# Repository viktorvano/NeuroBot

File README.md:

# NeuroBot
This is open source robot with a deep neural network.
Deep Neural Network can be configured by a file content.

Training Data are in "training.txt".

Topology is in "topology.txt".

Demo video: https://www.youtube.com/watch?v=UL9_z_reCno

Android App: https://play.google.com/store/apps/details?id=com.cyberpunktech.RobotController.app

If the content of "weights.txt" file is deleted, the neural network automatically retrain itself again.
If the number of weights in the weights.txt file matches with topology, the Neural Network just loads them, and runs.

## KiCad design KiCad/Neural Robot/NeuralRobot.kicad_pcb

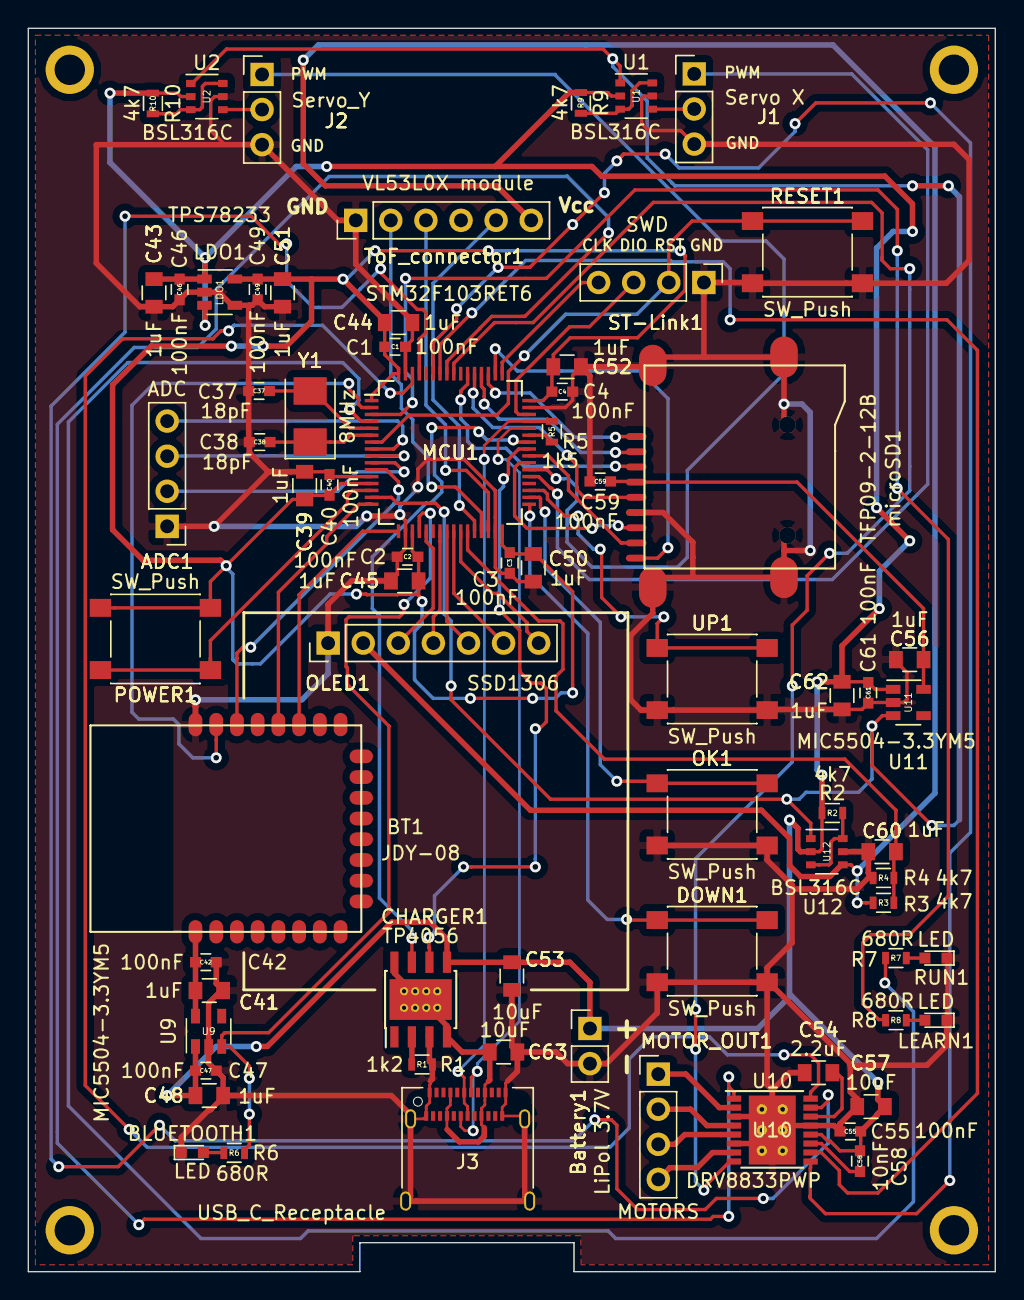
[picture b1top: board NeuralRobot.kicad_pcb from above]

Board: 2 copper layers, 70.0 x 90.0 mm, 70 parts (0 on the bottom side), 71 nets.

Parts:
ADC1: ADC; Socket_Strip_Straight_1x04_Pitch2.54mm
BLUETOOTH1: LED; LED_0603
BT1: JDY-08; JDY-08_module
Battery1: LiPol 3.7V; Socket_Strip_Straight_1x02_Pitch2.54mm
C1, C2, C3, C4, C40, C42, C46, C47, C49, C55, C59, C61: 100nF; C_0603
C37, C38: 18pF; C_0603
C39, C41, C43, C44, C45, C48, C50, C51, C52, C56, C60, C62: 1uF; C_0805
C53, C57, C63: 10uF; C_0805
C54: 2.2uF; C_0805
C58: 10nF; C_0603
CHARGER1: TP4056; HTSOP-8-1EP_3.9x4.9mm_Pitch1.27mm_ThermalVias_LargeCopper
DOWN1: SW_Push; SW_SPST_PTS645
J1: Servo X; Socket_Strip_Straight_1x03_Pitch2.54mm
J2: Servo_Y; Socket_Strip_Straight_1x03_Pitch2.54mm
J3: USB_C_Receptacle; USB_C_Receptacle_Amphenol_12401610E4-2A
LDO1: TPS78233; SOT-23-5
LEARN1: LED; LED_0603
MCU1: STM32F103RET6; LQFP-64_10x10mm_Pitch0.5mm
MOTOR_OUT1: MOTORS; Socket_Strip_Straight_1x04_Pitch2.54mm
OK1: SW_Push; SW_SPST_PTS645
OLED1: SSD1306; Socket_Strip_Straight_1x07_Pitch2.54mm
POWER1: SW_Push; SW_SPST_PTS645
R1: 1k2; R_0603
R2, R3, R4, R9, R10: 4k7; R_0603
R5: 1k5; R_0603
R6, R7, R8: 680R; R_0603
RESET1: SW_Push; SW_SPST_PTS645
RUN1: LED; LED_0603
ST-Link1: SWD; Socket_Strip_Straight_1x04_Pitch2.54mm
ToF_connector1: VL53L0X module; Socket_Strip_Straight_1x06_Pitch2.54mm
U1, U2, U12: BSL316C; TSOP-6_1.65x3.05mm_Pitch0.95mm
U9, U11: MIC5504-3.3YM5; SOT-23-5
U10: DRV8833PWP; HTSSOP-16-1EP_4.4x5mm_Pitch0.65mm_ThermalVias
UP1: SW_Push; SW_SPST_PTS645
Y1: 8MHz; Crystal_SMD_5032-2pin_5.0x3.2mm
microSD1: TFP09-2-12B; microSD_card_slot

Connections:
3V3_STM32: C1.2, C2.1, C3.1, C4.1, C39.2, C40.1, C44.2, C45.2, C49.2, C50.2, C51.2, C52.2, LDO1.5, MCU1.1, MCU1.13, MCU1.19, MCU1.32, MCU1.48, MCU1.64, POWER1.2
3V7: Battery1.1, C43.2, C46.2, C47.2, C48.2, C53.2, C55.1, C57.1, C58.2, C61.2, C62.2, CHARGER1.5, LDO1.1, LDO1.3, R2.1, R9.1, R10.1, U1.2, U2.2, U9.1, U10.12, U11.1, U12.2
5V: C63.2, CHARGER1.4, CHARGER1.8, CHARGER1.9, J3.A4, J3.A9, J3.B4, J3.B9
A1: MCU1.62, U10.16
A2: MCU1.61, U10.15
B1: MCU1.59, U10.9
B2: MCU1.58, U10.10
BATTERY_SENSE: C60.2, MCU1.27, R3.1, R4.2
BT_ENABLE: MCU1.20, R6.2, U9.3
BT_PWR: BT1.22, MCU1.11
BT_RST: BT1.23, MCU1.2
BT_Vcc: BT1.1, C41.2, C42.2, U9.5
BUTTON_DOWN: DOWN1.1, MCU1.33
BUTTON_OK: MCU1.34, OK1.1
BUTTON_UP: MCU1.35, UP1.1
CHARGING: CHARGER1.7, MCU1.42
CS: MCU1.26, OLED1.7
D+: J3.A6, J3.B6, MCU1.45, R5.1
D-: J3.A7, J3.B7, MCU1.44
DC: MCU1.25, OLED1.6
FULL: CHARGER1.6, MCU1.41
GND: ADC1.1, BLUETOOTH1.1, BT1.24, Battery1.2, C1.1, C2.2, C3.2, C4.2, C37.2, C38.2, C39.1, C40.2, C41.1, C42.1, C43.1, C44.1, C45.1, C46.1, C47.1, C48.1, C49.1, C50.1, C51.1, C52.1, C53.1, C54.2, C55.2, C56.1, C57.2, C59.1, C60.1, C61.1, C62.1, C63.1, CHARGER1.3, DOWN1.2, J1.3, J2.3, J3.A1, J3.A12, J3.B1, J3.B12, J3.S1, LDO1.2, LDO1.4, LEARN1.1, MCU1.12, MCU1.18, MCU1.31, MCU1.47, MCU1.63, OK1.2, OLED1.1, R1.2, R4.1, RESET1.2, RUN1.1, ST-Link1.1, ToF_connector1.1, U1.5, U2.5, U9.2, U10.3, U10.6, U10.13, U10.17, U11.2, U12.5, UP1.2, microSD1.6, microSD1.10
LED_RUN: MCU1.4, R7.2
LED_TRAINING: MCU1.3, R8.2
MOSFET_ENABLE: MCU1.15, U1.1, U2.1, U11.3, U12.1
MOSFET_OUT: OLED1.2, R3.2, ToF_connector1.6, U12.4
MOSI: MCU1.23, OLED1.4
MOTORS_ENABLE: MCU1.57, U10.1
unnamed: ADC1.2, MCU1.10
unnamed: ADC1.3, MCU1.9
unnamed: ADC1.4, MCU1.8
unnamed: BLUETOOTH1.2, R6.1
unnamed: C37.1, MCU1.5, Y1.2
unnamed: C38.1, MCU1.6, Y1.1
unnamed: C54.1, U10.14
unnamed: CHARGER1.2, R1.1
unnamed: J1.2, U1.4
unnamed: J2.2, U2.4
unnamed: LEARN1.2, R8.1
unnamed: MOTOR_OUT1.1, U10.2
unnamed: MOTOR_OUT1.2, U10.4
unnamed: MOTOR_OUT1.4, U10.7
unnamed: R2.2, U12.3, U12.6
unnamed: R7.1, RUN1.2
unnamed: R9.2, U1.3, U1.6
unnamed: R10.2, U2.3, U2.6
OUT2: MOTOR_OUT1.3, U10.5
PA0: MCU1.14, POWER1.1
PWM_X: J1.1, MCU1.37
PWM_Y: J2.1, MCU1.38
RST: MCU1.24, OLED1.5
RX: BT1.19, MCU1.17
Reset: MCU1.7, RESET1.1, ST-Link1.2
SCK: MCU1.21, OLED1.3
SCL: MCU1.29, ToF_connector1.2
SDA: MCU1.30, ToF_connector1.3
SDIO_CLK: MCU1.53, microSD1.5
SDIO_CMD: MCU1.54, microSD1.3
SDIO_D0: MCU1.39, microSD1.7
SDIO_D1: MCU1.40, microSD1.8
SDIO_D2: MCU1.51, microSD1.1
SDIO_D3: MCU1.52, microSD1.2
SD_DETECTION: MCU1.50, microSD1.9
SD_Vcc: C56.2, C59.2, U11.5, microSD1.4
SWCLK: MCU1.49, ST-Link1.4
SWDIO: MCU1.46, ST-Link1.3
TX: BT1.20, MCU1.16
ToF_Enable: MCU1.28, ToF_connector1.5
USB_ENABLE: MCU1.43, R5.2
VCP: C58.1, U10.11
nFAULT: MCU1.56, U10.8

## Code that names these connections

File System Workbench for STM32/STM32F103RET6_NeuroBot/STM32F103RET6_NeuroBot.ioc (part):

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Mcu.Name=STM32F103R(C-D-E)Tx
Mcu.Package=LQFP64
Mcu.UserName=STM32F103RETx
PA0-WKUP.GPIOParameters=GPIO_Label
PA0-WKUP.GPIO_Label=POWER_ON_MAIN
PA0-WKUP.Mode=SYS_WakeUp0
PA0-WKUP.Signal=SYS_WKUP
PA1.GPIOParameters=GPIO_Speed,GPIO_Label
PA1.GPIO_Label=MOSFET_Enable
PA1.GPIO_Speed=GPIO_SPEED_FREQ_HIGH
PA1.Signal=GPIO_Output
PA10.GPIOParameters=GPIO_Speed,GPIO_Label
PA10.GPIO_Label=USB_Enable
PA10.GPIO_Speed=GPIO_SPEED_FREQ_HIGH
PA10.Signal=GPIO_Output
PA11.Mode=Device
PA11.Signal=USB_DM
PA12.Mode=Device
PA12.Signal=USB_DP
PA13.Mode=Serial_Wire
PA13.Signal=SYS_JTMS-SWDIO
PA14.Mode=Serial_Wire
PA14.Signal=SYS_JTCK-SWCLK
PA15.GPIOParameters=GPIO_PuPd,GPIO_Label
PA15.GPIO_Label=SD_DETECTION
PA15.GPIO_PuPd=GPIO_PULLUP
PA15.Signal=GPIO_Input
PA2.Mode=Asynchronous
PA2.Signal=USART2_TX
PA3.Mode=Asynchronous
PA3.Signal=USART2_RX
PA4.GPIOParameters=GPIO_Speed,GPIO_Label
PA4.GPIO_Label=Bluetooth_Enable
PA4.GPIO_Speed=GPIO_SPEED_FREQ_HIGH
PA4.Signal=GPIO_Output
PA5.Mode=Simplex_Bidirectional_Master
PA5.Signal=SPI1_SCK
PA7.Mode=Simplex_Bidirectional_Master
PA7.Signal=SPI1_MOSI
PA8.GPIOParameters=GPIO_PuPd,GPIO_Label
PA8.GPIO_Label=Battery_Full
PA8.GPIO_PuPd=GPIO_PULLUP
PA8.Signal=GPIO_Input
PA9.GPIOParameters=GPIO_PuPd,GPIO_Label
PA9.GPIO_Label=Battery_Charging
PA9.GPIO_PuPd=GPIO_PULLUP
PA9.Signal=GPIO_Input
PB0.GPIOParameters=GPIO_Speed,PinState,GPIO_Label
PB0.GPIO_Label=OLED_CS
PB0.GPIO_Speed=GPIO_SPEED_FREQ_HIGH
PB0.PinState=GPIO_PIN_SET
PB0.Signal=GPIO_Output
PB1.GPIOParameters=GPIO_Label
PB1.GPIO_Label=BATTERY_SENSE
PB1.Signal=ADCx_IN9
PB10.Mode=I2C
PB10.Signal=I2C2_SCL
PB11.Mode=I2C
PB11.Signal=I2C2_SDA
PB12.GPIOParameters=GPIO_PuPd,GPIO_Label
PB12.GPIO_Label=BUTTON_DOWN
PB12.GPIO_PuPd=GPIO_PULLUP
PB12.Signal=GPIO_Input
PB13.GPIOParameters=GPIO_PuPd,GPIO_Label
PB13.GPIO_Label=BUTTON_OK
PB13.GPIO_PuPd=GPIO_PULLUP
PB13.Signal=GPIO_Input
PB14.GPIOParameters=GPIO_PuPd,GPIO_Label
PB14.GPIO_Label=BUTTON_UP
PB14.GPIO_PuPd=GPIO_PULLUP
PB14.Signal=GPIO_Input
PB2.GPIOParameters=GPIO_Speed,GPIO_Label
PB2.GPIO_Label=ToF_Enable
PB2.GPIO_Speed=GPIO_SPEED_FREQ_HIGH
PB2.Signal=GPIO_Output
PB4.GPIOParameters=GPIO_PuPd,GPIO_Label
PB4.GPIO_Label=Motor_nFault
PB4.GPIO_PuPd=GPIO_PULLUP
PB4.Signal=GPIO_Input
PB5.GPIOParameters=GPIO_Speed,GPIO_Label
PB5.GPIO_Label=Motor_Enable
PB5.GPIO_Speed=GPIO_SPEED_FREQ_HIGH
PB5.Signal=GPIO_Output
PB6.GPIOParameters=GPIO_Speed,GPIO_Label
PB6.GPIO_Label=Motor_B2
PB6.GPIO_Speed=GPIO_SPEED_FREQ_HIGH
PB6.Signal=GPIO_Output
PB7.GPIOParameters=GPIO_Speed,GPIO_Label
PB7.GPIO_Label=Motor_B1
PB7.GPIO_Speed=GPIO_SPEED_FREQ_HIGH
PB7.Signal=GPIO_Output
PB8.GPIOParameters=GPIO_Speed,GPIO_Label
PB8.GPIO_Label=Motor_A2
PB8.GPIO_Speed=GPIO_SPEED_FREQ_HIGH
PB8.Signal=GPIO_Output
PB9.GPIOParameters=GPIO_Speed,GPIO_Label
PB9.GPIO_Label=Motor_A1
PB9.GPIO_Speed=GPIO_SPEED_FREQ_HIGH
PB9.Signal=GPIO_Output
PC0.Signal=ADCx_IN10
PC1.Signal=ADCx_IN11
PC10.Mode=SD_4_bits_Wide_bus
PC10.Signal=SDIO_D2
PC11.Mode=SD_4_bits_Wide_bus
PC11.Signal=SDIO_D3
PC12.Mode=SD_4_bits_Wide_bus
PC12.Signal=SDIO_CK
PC13-TAMPER-RTC.GPIOParameters=PinState,GPIO_Label
PC13-TAMPER-RTC.GPIO_Label=Bluetooth_RESET
PC13-TAMPER-RTC.PinState=GPIO_PIN_SET
PC13-TAMPER-RTC.Signal=GPIO_Output
PC14-OSC32_IN.GPIOParameters=GPIO_Speed,GPIO_Label
PC14-OSC32_IN.GPIO_Label=LED_Training
PC14-OSC32_IN.GPIO_Speed=GPIO_SPEED_FREQ_HIGH
PC14-OSC32_IN.Signal=GPIO_Output
PC15-OSC32_OUT.GPIOParameters=GPIO_Speed,GPIO_Label
PC15-OSC32_OUT.GPIO_Label=LED_Run
PC15-OSC32_OUT.GPIO_Speed=GPIO_SPEED_FREQ_HIGH
PC15-OSC32_OUT.Signal=GPIO_Output
PC2.Signal=ADCx_IN12
PC3.GPIOParameters=PinState,GPIO_Label
PC3.GPIO_Label=Bluetooth_PWR
PC3.PinState=GPIO_PIN_SET
PC3.Signal=GPIO_Output
PC4.GPIOParameters=GPIO_Speed,GPIO_Label
PC4.GPIO_Label=OLED_RESET
PC4.GPIO_Speed=GPIO_SPEED_FREQ_HIGH
PC4.Signal=GPIO_Output
PC5.GPIOParameters=GPIO_Speed,GPIO_Label
PC5.GPIO_Label=OLED_DC
PC5.GPIO_Speed=GPIO_SPEED_FREQ_HIGH
PC5.Signal=GPIO_Output
PC6.Signal=S_TIM3_CH1
PC7.Signal=S_TIM3_CH2
PC8.Mode=SD_4_bits_Wide_bus
PC8.Signal=SDIO_D0
PC9.Mode=SD_4_bits_Wide_bus
PC9.Signal=SDIO_D1
PD0-OSC_IN.Mode=HSE-External-Oscillator
PD0-OSC_IN.Signal=RCC_OSC_IN
PD1-OSC_OUT.Mode=HSE-External-Oscillator
PD1-OSC_OUT.Signal=RCC_OSC_OUT
PD2.Mode=SD_4_bits_Wide_bus
PD2.Signal=SDIO_CMD
RCC.SYSCLKFreq_VALUE=72000000
RCC.SYSCLKSource=RCC_SYSCLKSOURCE_PLLCLK
board=STM32F103RET6_AIM_1.0

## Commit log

2018-12-24 First upload
    it contains Cpp project for Visual Studio, System Workbench, and PCB project for KiCad
2018-12-24 Updated readme
    Added content to Readme file
2018-12-24 Added Android link
    Edited readme, removed file contents examples, added android app link.
2018-12-24 Added Android App
    Android Studio BLE app
2018-12-25 Updated projects, added FreCad
    Added FreeCad project, updated Android App, and SWforSTM32.
    Now it sends a message via Bluetooth every 100 ms.
2018-12-25 3D model update
    Updated FreeCad 3D model for NeuroBot.
2019-01-11 STM code update
    Updated code for NeuroBot for STM32.
2019-01-11 Updated Freecad Model
    Now it fits well.
2019-01-11 Updated battery
    Updated max battery level condition.
2019-01-12 Updated battery code
    Now it shows a battery accurately.
2019-01-12 Battery update
    Better coeficient, to calculate voltage.
2019-01-13 Bluetooth update
    Now when the robot moves and bluetooth get disconnected robot stops.
    Also added a random function to rotate and move more randomly to see a behaviour, and helps to get out of corners.
2019-01-21 Fall detection
    Now it tilts down ToF sensor to avoid a fall from the edge.
2019-01-30 Android update
    Now BLE scan, works on new Android devices.
2019-02-04 Servo tuning
    I just tuned the X servo to the middle.
2019-02-08 SD files upload
    Uploaded files for NeuroBot.
2019-02-09 Removed old screenshots
    Old screenshots from unrelated project.
2019-02-09 Placed related screenshots
    only those to project related.
2019-02-09 deleting old pics
    these are not related.
2019-02-10 Added youtube link
    Added a demo video.
2019-02-10 fixed mistake
2019-02-10 FIxed DMA and Battery issue
    I forgot to add 4th ADC to DMA, so those ADC measurements were mixing in a bigger buffer for DMA.
    Now it is fixed.
2019-02-10 Small function modification.
    Removed unnecessary call.
2019-03-03 Battery update
    just lowered down the full bettery voltage, because of the load on the cell during rung mode.
2019-03-24 Fixed typo
    targerValue to targetValue
2019-03-30 Changed ADC sampling
    This will unload the DMA from too many interrupts.
2019-04-05 Removed random delays.
    Now the neural net time of movements are based on neural net's decision.
2019-04-11 Movement update
    Robot needs approximately 200ms to start moving.
2019-04-20 overheat check
    moved a function to more reasonable place
2019-04-20 fixed battery bug
    Now it should refresh battery status after unplugging the charging cable automatically.
2019-04-20 motor_direction()
    Modified the function a little bit.
    Works the same, looks better.
2019-04-22 Added output to LCD
    Now user can see the output decision on the OLED display.
2019-04-24 Print output
    Now it prints outputs of Neural Net for left left motor and right motor. They are marked as L: 0.995 and R: 0.423
2019-04-27 Stopwatch in training mode
    Now you can see how long does it take to train a NN.
2019-04-30 SD files update
    Now the "Neural Network.exe" prints out a training time.
    Also I have used a more complex topology.
2019-05-04 Updated motor function
    Now the robot can turn more accordingly to its decision.
2019-05-04 Tuned the turning time.
    It was turning too much before.
2019-10-31 Updated to 1.6
    Changed Accelerometer to Gravity sensor.
